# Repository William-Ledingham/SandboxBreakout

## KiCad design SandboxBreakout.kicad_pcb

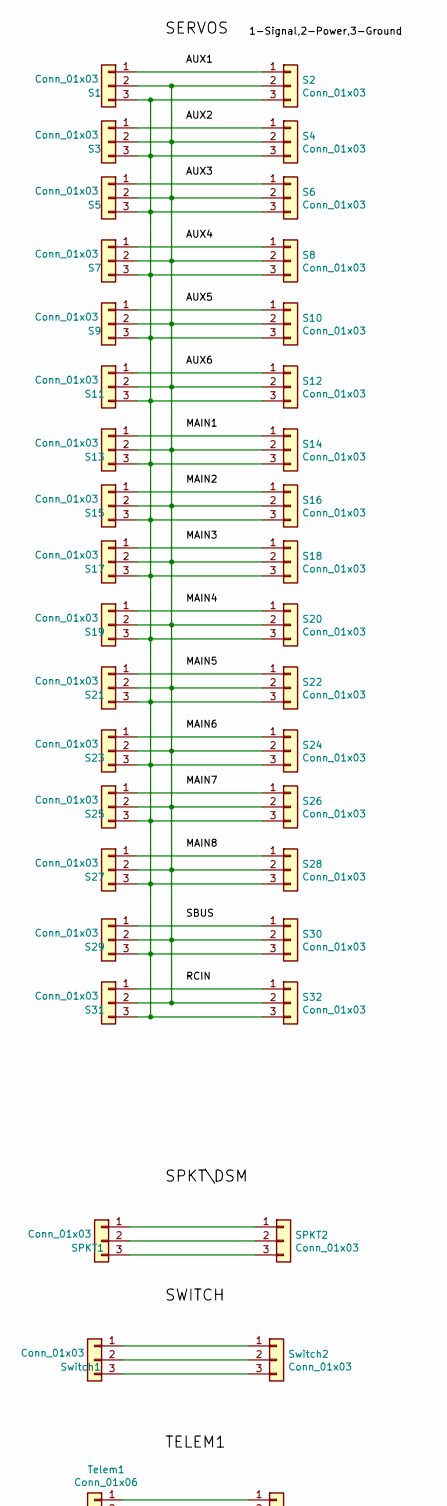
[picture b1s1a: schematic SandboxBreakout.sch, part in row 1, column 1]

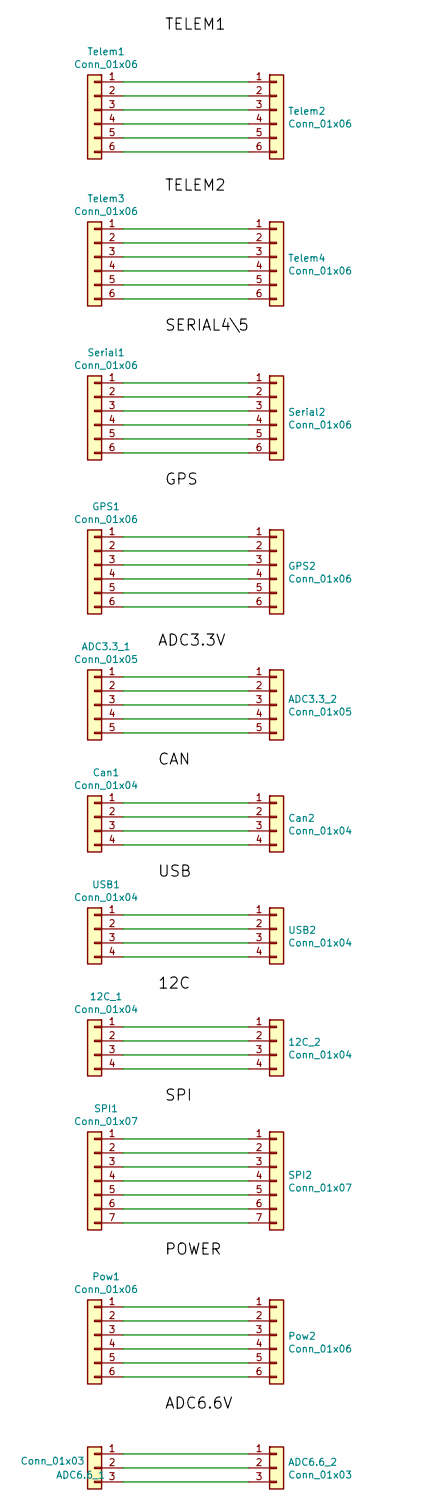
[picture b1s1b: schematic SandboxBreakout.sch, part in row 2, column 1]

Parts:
12C_1, 12C_2: Conn_01x04; JST_GH_BM04B-GHS-TBT_1x04-1MP_P1.25mm_Vertical
ADC3.3_1, ADC3.3_2: Conn_01x05; JST_GH_BM05B-GHS-TBT_1x05-1MP_P1.25mm_Vertical
ADC6.6_1, ADC6.6_2: Conn_01x03; JST_GH_BM03B-GHS-TBT_1x03-1MP_P1.25mm_Vertical
Can1, Can2: Conn_01x04; JST_GH_BM04B-GHS-TBT_1x04-1MP_P1.25mm_Vertical
GPS1, GPS2: Conn_01x06; JST_GH_BM06B-GHS-TBT_1x06-1MP_P1.25mm_Vertical
Pow1, Pow2: Conn_01x06; JST_GH_BM06B-GHS-TBT_1x06-1MP_P1.25mm_Vertical
S1, S2, S3, S4, S5, S6, S7, S8, S9, S10, S11, S12, S13, S14, S15, S16, S17, S18, S19, S20, S21, S22, S23, S24, S25, S26, S27, S28, S29, S30, S31, S32: Conn_01x03; PinHeader_1x03_P2.54mm_Vertical
SPI1, SPI2: Conn_01x07; JST_GH_BM07B-GHS-TBT_1x07-1MP_P1.25mm_Vertical
SPKT1, SPKT2: Conn_01x03; JST_GH_BM03B-GHS-TBT_1x03-1MP_P1.25mm_Vertical
Serial1, Serial2: Conn_01x06; JST_GH_BM06B-GHS-TBT_1x06-1MP_P1.25mm_Vertical
Switch1, Switch2: Conn_01x03; JST_GH_BM03B-GHS-TBT_1x03-1MP_P1.25mm_Vertical
Telem1, Telem2, Telem3, Telem4: Conn_01x06; JST_GH_BM06B-GHS-TBT_1x06-1MP_P1.25mm_Vertical
USB1, USB2: Conn_01x04; JST_GH_BM04B-GHS-TBT_1x04-1MP_P1.25mm_Vertical

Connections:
unnamed: 12C_1.1, 12C_2.1
unnamed: 12C_1.2, 12C_2.2
unnamed: 12C_1.3, 12C_2.3
unnamed: 12C_1.4, 12C_2.4
unnamed: ADC3.3_1.1, ADC3.3_2.1
unnamed: ADC3.3_1.2, ADC3.3_2.2
unnamed: ADC3.3_1.3, ADC3.3_2.3
unnamed: ADC3.3_1.4, ADC3.3_2.4
unnamed: ADC3.3_1.5, ADC3.3_2.5
unnamed: ADC6.6_1.1, ADC6.6_2.1
unnamed: ADC6.6_1.2, ADC6.6_2.2
unnamed: ADC6.6_1.3, ADC6.6_2.3
unnamed: Can1.1, Can2.1
unnamed: Can1.2, Can2.2
unnamed: Can1.3, Can2.3
unnamed: Can1.4, Can2.4
unnamed: GPS1.1, GPS2.1
unnamed: GPS1.2, GPS2.2
unnamed: GPS1.3, GPS2.3
unnamed: GPS1.4, GPS2.4
unnamed: GPS1.5, GPS2.5
unnamed: GPS1.6, GPS2.6
unnamed: Pow1.1, Pow2.1
unnamed: Pow1.2, Pow2.2
unnamed: Pow1.3, Pow2.3
unnamed: Pow1.4, Pow2.4
unnamed: Pow1.5, Pow2.5
unnamed: Pow1.6, Pow2.6
unnamed: S1.1, S2.1
unnamed: S1.2, S2.2, S3.2, S4.2, S5.2, S6.2, S7.2, S8.2, S9.2, S10.2, S11.2, S12.2, S13.2, S14.2, S15.2, S16.2, S17.2, S18.2, S19.2, S20.2, S21.2, S22.2, S23.2, S24.2, S25.2, S26.2, S27.2, S28.2, S29.2, S30.2, S31.2, S32.2
unnamed: S1.3, S2.3, S3.3, S4.3, S5.3, S6.3, S7.3, S8.3, S9.3, S10.3, S11.3, S12.3, S13.3, S14.3, S15.3, S16.3, S17.3, S18.3, S19.3, S20.3, S21.3, S22.3, S23.3, S24.3, S25.3, S26.3, S27.3, S28.3, S29.3, S30.3, S31.3, S32.3
unnamed: S3.1, S4.1
unnamed: S5.1, S6.1
unnamed: S7.1, S8.1
unnamed: S9.1, S10.1
unnamed: S11.1, S12.1
unnamed: S13.1, S14.1
unnamed: S15.1, S16.1
unnamed: S17.1, S18.1
unnamed: S19.1, S20.1
unnamed: S21.1, S22.1
unnamed: S23.1, S24.1
unnamed: S25.1, S26.1
unnamed: S27.1, S28.1
unnamed: S29.1, S30.1
unnamed: S31.1, S32.1
unnamed: SPI1.1, SPI2.1
unnamed: SPI1.2, SPI2.2
unnamed: SPI1.3, SPI2.3
unnamed: SPI1.4, SPI2.4
unnamed: SPI1.5, SPI2.5
unnamed: SPI1.6, SPI2.6
unnamed: SPI1.7, SPI2.7
unnamed: SPKT1.1, SPKT2.1
unnamed: SPKT1.2, SPKT2.2
unnamed: SPKT1.3, SPKT2.3
unnamed: Serial1.1, Serial2.1
unnamed: Serial1.2, Serial2.2
unnamed: Serial1.3, Serial2.3
unnamed: Serial1.4, Serial2.4
unnamed: Serial1.5, Serial2.5
unnamed: Serial1.6, Serial2.6
unnamed: Switch1.1, Switch2.1
unnamed: Switch1.2, Switch2.2
unnamed: Switch1.3, Switch2.3
unnamed: Telem1.1, Telem2.1
unnamed: Telem1.2, Telem2.2
unnamed: Telem1.3, Telem2.3
unnamed: Telem1.4, Telem2.4
unnamed: Telem1.5, Telem2.5
unnamed: Telem1.6, Telem2.6
unnamed: Telem3.1, Telem4.1
unnamed: Telem3.2, Telem4.2
unnamed: Telem3.3, Telem4.3
unnamed: Telem3.4, Telem4.4
unnamed: Telem3.5, Telem4.5
unnamed: Telem3.6, Telem4.6
unnamed: USB1.1, USB2.1
unnamed: USB1.2, USB2.2
unnamed: USB1.3, USB2.3
unnamed: USB1.4, USB2.4

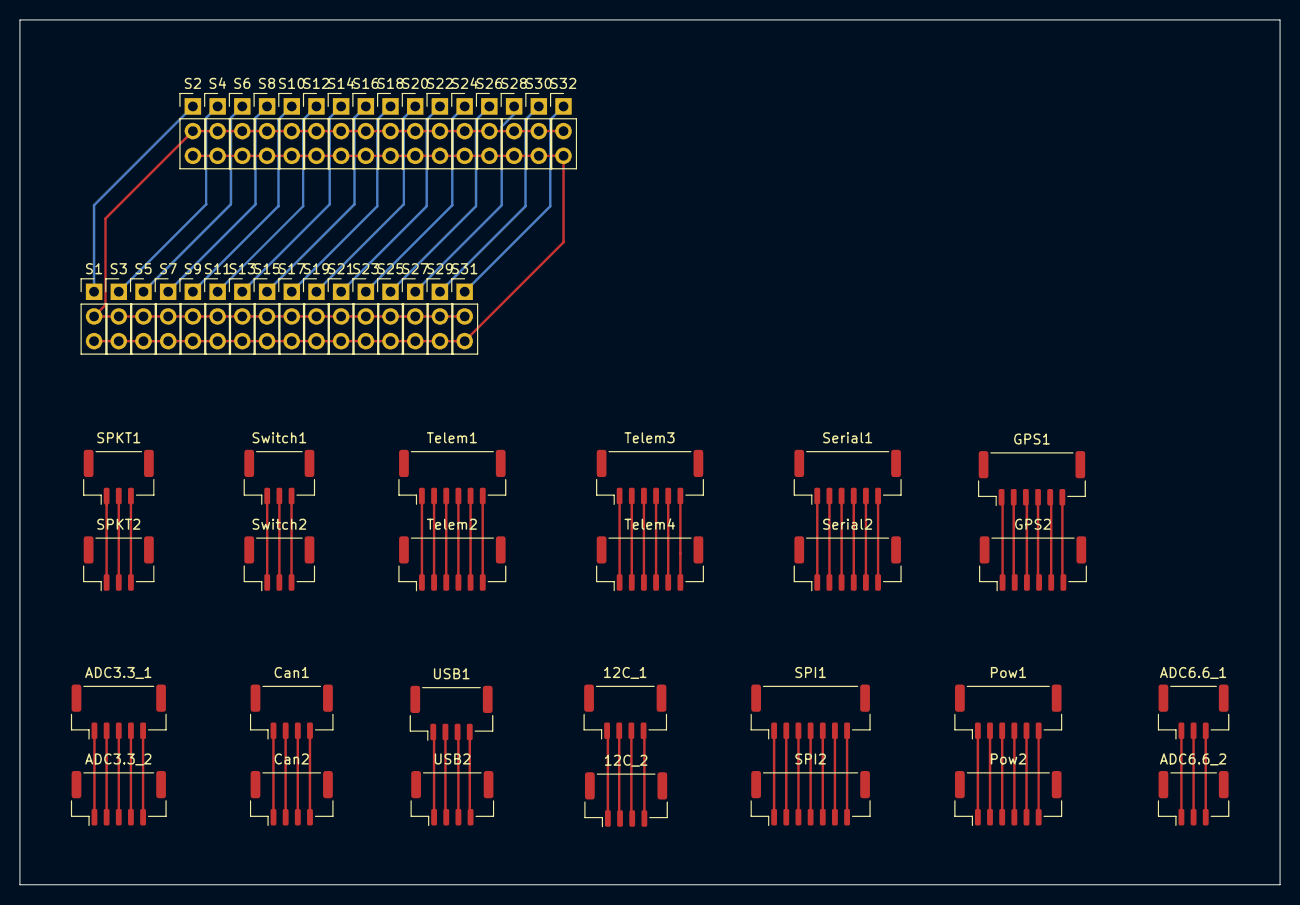
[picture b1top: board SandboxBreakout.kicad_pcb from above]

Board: 2 copper layers, 129.5 x 88.9 mm, 58 parts (0 on the bottom side), 81 nets.

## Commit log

2021-10-15 Update gitignore.
2021-10-15 Adding schematic.
2021-10-15 Adding KiCad files.
2021-10-16 test commit
2021-10-23 pixhawk connections added
2021-10-30 Started Pcbnew, servo connectors all scrambled
2021-11-20 Board Draft 1.0
2021-11-27 flipped a footprint
2021-11-27 Updated labels
2021-11-27 Added gerber and drill files
